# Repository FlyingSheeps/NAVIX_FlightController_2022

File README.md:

# NAVIX_FlightController_2022
Flying robots club NAVIX at Nagoya University joined the competition with this flight controller system.

## NAVIX-X4_Machina.xlsm  
機体設計に用いた諸元などを記載  

## NAVIX-X4_Machina  
製図関係データ．AutoCADがあれば.scrファイルをそのまま読み込める． 

## Machina_program  
ArduinoIDE用プログラム．ESP32にUSBシリアル変換を用いて書き込む．  
ライブラリとかは各自の環境で用意してください．現状そのまま書き込めないので注意．  
20221225：追記　最新版BolderFlightSystems/SBUSには対応していません．  
簡単には，SbusRxのコンストラクタの記述が変わって引数に&Serial1の他rxpin,txpin,trueが必要です．

## machina_PCB  
ESP32を用いたフライトコントローラー基板．  
microSDスロット  
I2C  
SBUS端子  
PWM6端子  
LED2個2系統  
ブートボタン  
リセットボタン  
ESCからの電源をマイコン向け3.3Vに降圧する電源系  
を備える．  
JLCPCBにmachinev2.zip渡して0.6mm厚二層で頼むと同じやつが届くよ．    
パーツは全て秋月で購入可能．

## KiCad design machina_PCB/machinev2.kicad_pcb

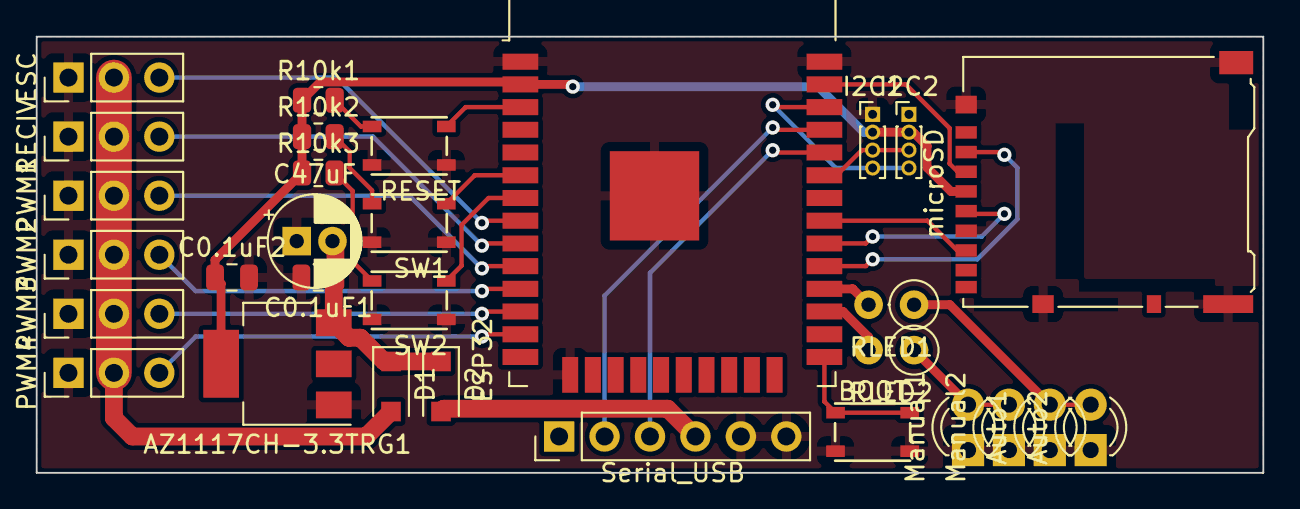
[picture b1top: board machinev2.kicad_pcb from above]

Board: 2 copper layers, 68.6 x 24.4 mm, 30 parts (0 on the bottom side), 30 nets.

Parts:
AZ1117CH-3.3TRG1: LM317_SOT-223; SOT-223-3_TabPin2
Auto1, Auto2: LED; LED_D3.0mm
BOOT: SW_DIP_x01; SKRPACE010
C0.1uF1, C0.1uF2: C; C_0805_2012Metric
C47uF: C; CP_Radial_D5.0mm_P2.00mm
D1, D2: MBR1020VL; D_SOD-123F
ESC: Conn_01x03; PinHeader_1x03_P2.54mm_Vertical
ESP32: ESP32-WROOM-32
I2C1, I2C2: Conn_01x04; PinHeader_1x04_P1.00mm_Vertical
Manual1, Manual2: LED; LED_D3.0mm
PWM1, PWM2, PWM3, PWM4: Conn_01x03; PinHeader_1x03_P2.54mm_Vertical
R10k1, R10k2, R10k3: R; R_0805_2012Metric
RECIV: Conn_01x03; PinHeader_1x03_P2.54mm_Vertical
RESET: SW_DIP_x01; SKRPACE010
RLED1, RLED2: R; R_Axial_DIN0207_L6.3mm_D2.5mm_P2.54mm_Vertical
SW1, SW2: SW_DIP_x01; SKRPACE010
Serial_USB: Conn_01x06; PinHeader_1x06_P2.54mm_Vertical
microSD: Micro_SD_Card_Det_Hirose_DM3AT; microSD_HC_Hirose_DM3AT-SF-PEJM5

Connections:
+3V3: AZ1117CH-3.3TRG1.2 (VO), C0.1uF2.1, ESP32.2 (VDD), I2C1.2, I2C2.2, R10k1.1, R10k2.1, R10k3.1, microSD.4 (VDD)
+5V: D1.2 (A), ESC.2, PWM1.2, PWM2.2, PWM3.2, PWM4.2, RECIV.2
BOOT: BOOT.3, BOOT.4, ESP32.25 (IO0)
CS: ESP32.29 (IO5), microSD.2 (DAT3/CD)
EN: ESP32.3 (EN), RESET.3
ESC: ESC.3, ESP32.8 (IO32)
GND: AZ1117CH-3.3TRG1.1 (ADJ), Auto1.1 (K), Auto2.1 (K), BOOT.1, BOOT.2, C0.1uF1.2, C0.1uF2.2, C47uF.1, ESC.1, ESP32.1 (GND), ESP32.15 (GND), ESP32.38 (GND), ESP32.39 (GND), I2C1.1, I2C2.1, Manual1.1 (K), Manual2.1 (K), PWM1.1, PWM2.1, PWM3.1, PWM4.1, RECIV.1, RESET.1, RESET.2, SW1.1, SW1.2, SW2.1, SW2.2, Serial_USB.5, Serial_USB.6, microSD.6 (VSS), microSD.11 (SHIELD)
LED_AUTO: ESP32.28 (IO17), RLED1.2
LED_MANUAL: ESP32.27 (IO16), RLED2.2
MISO: ESP32.31 (IO19), microSD.7 (DAT0)
MOSI: ESP32.37 (IO23), microSD.3 (CMD)
unnamed: AZ1117CH-3.3TRG1.3 (VI), C0.1uF1.1, C47uF.2, D1.1 (K), D2.1 (K)
unnamed: Auto1.2 (A), Auto2.2 (A), RLED1.1
unnamed: Manual1.2 (A), Manual2.2 (A), RLED2.1
unnamed: R10k1.2, RESET.4
unnamed: R10k2.2, SW1.4
unnamed: R10k3.2, SW2.4
PWM1: ESP32.10 (IO25), PWM1.3
PWM2: ESP32.11 (IO26), PWM2.3
PWM3: ESP32.12 (IO27), PWM3.3
PWM4: ESP32.13 (IO14), PWM4.3
RECIV: ESP32.9 (IO33), RECIV.3
RXD0: ESP32.34 (RXD0/IO3), Serial_USB.3
SCK: ESP32.30 (IO18), microSD.5 (CLK)
SCL: ESP32.36 (IO22), I2C1.4, I2C2.4
SDA: ESP32.33 (IO21), I2C1.3, I2C2.3
SW1: ESP32.6 (IO34), SW1.3
SW2: ESP32.7 (IO35), SW2.3
TXD0: ESP32.35 (TXD0/IO1), Serial_USB.2
VBUS: D2.2 (A), Serial_USB.4

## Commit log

2022-11-08 20221108
2022-11-08 20221108-2
2022-11-08 20221108n2
2022-11-08 20221108n3
2022-11-08 20221108n4
2022-11-10 mod readme
